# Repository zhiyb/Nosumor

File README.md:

# USB Mix

Design a small USB keyboard for playing [osu!](https://osu.ppy.sh/): [Blog posts](https://zhiyb.wordpress.com/category/cc/embedded/nosumor/)

In addition to mandatory keyboard functionalities, USB audio and Micro SD support are also added. So it's now called USB Mix.

The PCB layout was made compatible with [the original Nosumor v3 casing](http://noodlefighter.com/工作日志/log_nono/), which sells on [the official osu! store](https://osu.ppy.sh/store/product/20).

However, as a hobby project for learning USB framework and achieving high performance, the parts used in this design are probably unnecessarily expensive.

## Features

- USB 2.0 high-speed connection with 8kHz polling rate
- 5 switches (2x Cherry MX switches & 3x tactile switches)
- RGB lighting!
- Audio output through headphone jack using USB audio class 2
- Micro SD card reader
- Application for dynamic reconfiguration and firmware upgrade

### Planned features

- Audio input (MIC) through headphone jack
- MPU-9250 9-axis motion sensor
- ADC waveform capture
- DAC waveform generation

## PCB features

- 50×50 (mm) board area
- 2 mechanical keyboard switches (Cherry MX RGB compatible) and 3 tactile buttons
- Keycap and bottom-side RGB lighting
- STM32F722RE Cortex-M7 high performance MCU @216MHz
- USB 2.0 high-speed PHY USB3370
- 3.5mm audio jack with TLV320AIC3110 audio codec
- InvenSense MPU-9250 9-axis motion sensor
- On-board FT2232D connected to UART & JTAG for debugging
- Test points for 2xADC & 1xDAC
- Extension UART port with 3.3V power

Gerber files for PCB manufacturer Seeed Studio provided.

## Estimated costs

Configuration | Cost
---|---
Basic keyboard | £20
With audio and Micro SD slot | £30
Also with debugging USB port | £38

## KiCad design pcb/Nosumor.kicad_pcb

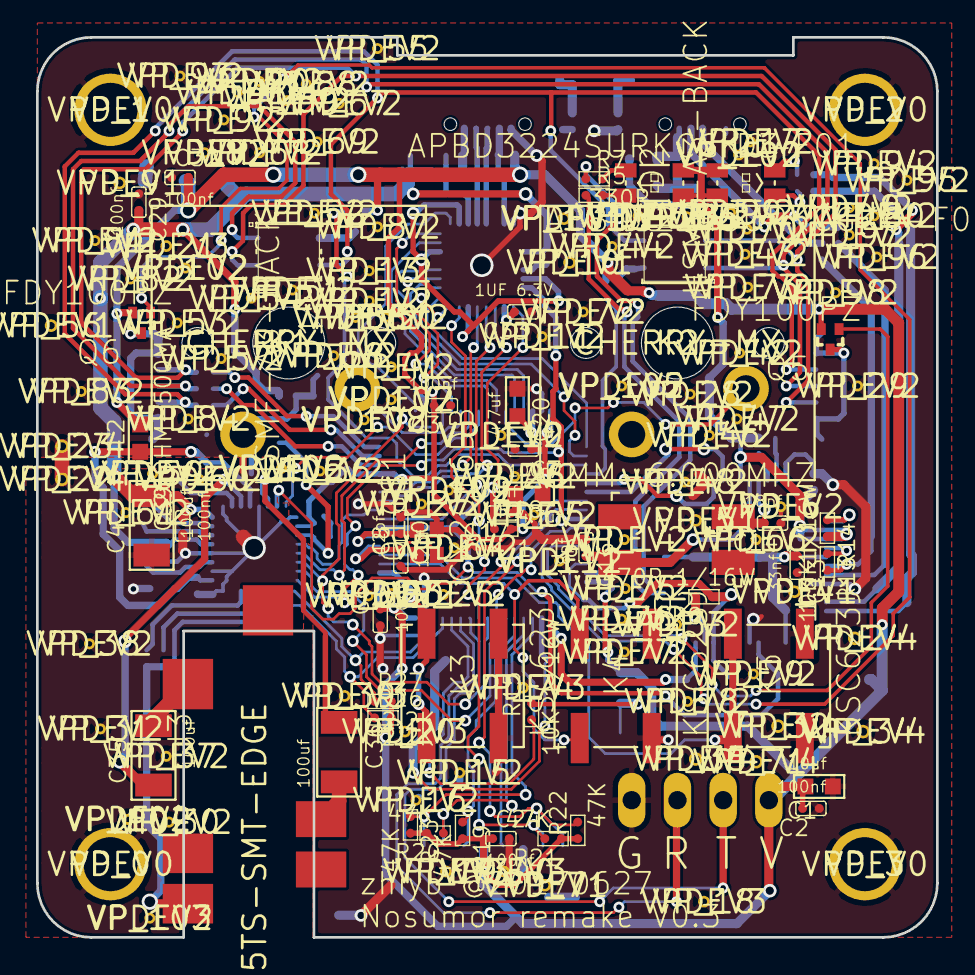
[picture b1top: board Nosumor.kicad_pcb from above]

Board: 2 copper layers, 50.0 x 50.0 mm, 223 parts (0 on the bottom side), 105 nets.

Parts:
3V3: TPB1,27; B1_27
BOOT316: 0R-JUMPB; B0R-JMP
C1, C23, C27, C37, C40: 10uf; C0603
C2, C3, C4, C5, C6, C9, C15, C17, C18, C19, C21, C22, C24, C25, C26, C28, C29, C31, C32, C38, C39, C41, C43, C44: 100nf; C0402
C7, C20: 4.7uf; C0603
C8, C10: 12pf; C0402
C11: 10nf; C0402
C12, C30, C33: 1UF 6.3V; C0402
C13: 33nf; C0402
C14, C16: 18pf; C0402
C34: 470nf; C0402
C35, C36, C42: 100uf; C1206
CLK316: TPB1,27; B1_27
D1, D2: HSMF-A3-BACK
D3, D5: APBD3224SURKCGKC-F01; 1210
D4, D6: MSL0104RGBU1; 2709
DIO316: TPB1,27; B1_27
GND316: TPB1,27; B1_27
IC1: STM32F722RET; LQFP64
IC2: REG1117; SOT223
IC3: TPS77018; SOT23-DBV
J1, J4: 629105136821
J2: 693071010811
J3: SJ-43515TS-SMT-EDGE; SJ-4351*-SMT-MIRRORED-EDGE
K1, K2: CHERRY-MX
K3, K4, K5: KSC623J; KSC-J
L1, L2, L3: 120OHM-500MA; L0603
Q1G$1: CX2016DB
Q2: ABMM-6.000MHZ; ABMM
Q3, Q4, Q5, Q6: FDY100PZ; SC-89
R4, R5, R6, R7: 330R; R0402
R8, R9: 470R 1/16W; R0402
R10, R11, R12: 150R; R0402
R13: 1.5K; R0402
R14, R15, R18, R28, R30: 10K 1/16W; R0402
R16, R17: 22R; R0402
R19, R20, R21, R22, R23: 47K; R0402
R26, R27, R31: 2.2K; R0402
R29: 20K; R0402
RST316: TPB1,27; B1_27
SLM316: TPB1,27; B1_27
SLP316: TPB1,27; B1_27
SRM316: TPB1,27; B1_27
SRP316: TPB1,27; B1_27
U1: LQFP48
U2: USB3370; QFN32
U3: TLV320AIC3110; VQFN32
UART316: 1X04
VP_0, VP_1, VP_2, VP_3: VPDEV0; VPAC0
VP_4, VP_5, VP_7, VP_9, VP_10, VP_56, VP_101: VPDEV1; VPAC1
VP_6, VP_8, VP_11, VP_12, VP_13, VP_14, VP_15, VP_16, VP_17, VP_25, VP_26, VP_27, VP_28, VP_29, VP_30, VP_31, VP_33, VP_36, VP_37, VP_38, VP_41, VP_42, VP_43, VP_44, VP_45, VP_46, VP_47, VP_48, VP_49, VP_50, VP_51, VP_52, VP_53, VP_54, VP_55, VP_57, VP_58, VP_59, VP_60, VP_61, VP_62, VP_63, VP_64, VP_65, VP_66, VP_67, VP_68, VP_69, VP_70, VP_72, VP_73, VP_75, VP_76, VP_77, VP_78, VP_79, VP_80, VP_81, VP_82, VP_83, VP_84, VP_85, VP_86, VP_87, VP_88, VP_89, VP_90, VP_91, VP_92, VP_93, VP_94, VP_95, VP_96, VP_97, VP_98, VP_99, VP_100, VP_102, VP_103, VP_104, VP_105, VP_106, VP_107, VP_108, VP_109, VP_110, VP_111: VPDEV2; VPAC2
VP_18, VP_19, VP_20, VP_21, VP_39, VP_40, VP_74: VPDEV3; VPAC3
VP_22, VP_23, VP_24, VP_32, VP_34, VP_35, VP_71: VPDEV4; VPAC4

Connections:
+1V8: C26.2, IC3.5, U3.3
+3V3: 3V3.TP, BOOT316.1, C1.2, C2.2, C3.2, C4.2, C5.2, C6.2, C7.2, C11.2, C12.2, C15.2, C24.1, C25.2, C32.2, IC1.1, IC1.13, IC1.19, IC1.32, IC1.48, IC1.64, IC2.2, J2.4, L2.2, Q3.3, Q4.3, Q5.3, Q6.3, R18.2, R19.2, R20.2, R21.1, R22.1, R23.2, R26.2, R27.2, R30.2, U3.2, UART316.1
+5V: C29.2, C38.2, C39.2, C40.2, C41.2, C42.2, IC2.3, IC3.1, L3.1, R29.2, U2.11, U3.21, U3.24
/AIC_BCLK: IC1.42, IC1.55, U3.7
/AIC_DIN: IC1.23, U3.5
/AIC_DOUT: IC1.9, U3.4
/AIC_GPIO: IC1.24, U3.32
/AIC_SCL: IC1.61, R26.1, U3.10
/AIC_SDA: IC1.62, R27.1, U3.9
/AIC_WCLK: IC1.20, IC1.56, U3.6
/BOOT0: IC1.60, R15.1
/DBG_5V: C19.2, C22.2, C23.2, D3.1, D3.3, D5.1, D5.3, L1.1, R9.2, R14.2, U1.3, U1.4, U1.42
/DBG_RXD: IC1.37, U1.39
/DBG_RX_LED: R7.1, U1.28
/DBG_SWD_LED1: R6.1, U1.12
/DBG_SWD_LED2: R4.1, U1.11
/DBG_TXD: IC1.38, U1.40
/DBG_TX_LED: R5.1, U1.27
/KEY_1: IC1.22, K1.SW1
/KEY_2: IC1.27, K2.SW1
/KEY_3: IC1.2, K3.1, K3.3
/KEY_4: IC1.3, K4.1, K4.3
/KEY_5: IC1.4, K5.1, K5.3
/LED_1: IC1.35, Q3.1
/LED_2: IC1.36, Q4.1
/LED_3: IC1.44, Q5.1
/LED_4: IC1.43, Q6.1
/MCLK: IC1.41, U2.15, U3.8
/MMC_CD: IC1.50, J2.10, J2.10-1
/MMC_CLK: IC1.53, J2.5
/MMC_CMD: IC1.54, J2.3, R19.1
/MMC_D0: IC1.39, J2.7, R21.2
/MMC_D1: IC1.40, J2.8, R22.2
/MMC_D2: IC1.51, J2.1, R23.1
/MMC_D3: IC1.52, J2.2, R20.1
/N$1: C35.2, J3.2
/N$4: J4.3, U2.5
/N$5: J4.2, U2.4
/N$6: J4.4, R30.1, U2.7
/N$7: SLP316.TP, U3.22
/N$8: J1.2, R16.2
/N$9: R13.2, R17.1, U1.7
/N$10: C13.1, U1.6, U1.14, U1.31
/N$11: C9.1, R9.1, U1.46
/N$12: D3.4, R6.2
/N$13: C18.2, J1.1, L1.2
/N$14: R13.1, U1.5
/N$15: R16.1, U1.8
/N$16: J1.3, R17.2
/N$17: R14.1, U1.2
/N$18: C14.2, Q2.1, U1.44
/N$19: C16.2, Q2.3, U1.43
/N$20: D5.4, R7.2
/N$21: D5.2, R5.2
/N$23: D3.2, R4.2
/N$24: C8.2, IC1.5, Q1G$1.1
/N$25: R8.2, U1.23
/N$26: C10.2, IC1.6, Q1G$1.3
/N$27: BOOT316.2, R15.2
/N$28: D6.1, D6.2, D6.6, D6.7, Q6.2
/N$29: C20.2, IC1.30
/N$30: SLM316.TP, U3.19
/N$31: C43.2, J4.1, L3.2
/N$32: R29.1, U2.13
/N$33: C30.2, U2.2, U2.14, U2.22, U2.30
/N$34: D1.2, Q3.2
/N$36: C33.2, U2.18
/N$37: R28.2, U2.3
/N$38: D4.1, D4.2, D4.6, D4.7, Q5.2
/N$39: D2.2, Q4.2
/N$40: D1.3, D2.3, D4.5, D6.5, R12.2
/N$41: D1.1, D2.1, D4.4, D6.4, R11.2
/N$42: D1.4, D2.4, D4.3, D6.3, R10.2
/N$44: SRP316.TP, U3.26
/N$45: SRM316.TP, U3.23
/N$46: C34.1, U3.14
/N$48: C36.1, U3.30
/N$49: R31.1, U3.12
/N$50: C35.1, U3.27
/N$51: C27.2, C28.2, C31.2, C37.2, L2.1, U3.17, U3.28
/RGB2_B: IC1.16, R10.1
/RGB2_G: IC1.15, R12.1
/RGB2_R: IC1.14, R11.1
/SRST_N: C17.2, IC1.7, R18.1, RST316.TP, U1.17, U2.17, U3.31
/SWCLK: CLK316.TP, IC1.49, U1.24
/SWDIO: DIO316.TP, IC1.46, R8.1, U1.22
/UART_RX: IC1.59, UART316.3
/UART_TX: IC1.58, UART316.2
/ULPI_CLK: IC1.21, U2.27
/ULPI_D0: IC1.17, U2.1
/ULPI_D1: IC1.25, U2.32
/ULPI_D2: IC1.26, U2.31
/ULPI_D3: IC1.28, U2.28
/ULPI_D4: IC1.29, U2.26
/ULPI_D5: IC1.33, U2.25
/ULPI_D6: IC1.34, U2.24
/ULPI_D7: IC1.57, U2.23
/ULPI_DIR: IC1.10, U2.19
/ULPI_NXT: IC1.11, U2.21
/ULPI_STP: IC1.8, U2.20
GND: BOOT316.3, C1.1, C2.1, C3.1, C4.1, C5.1, C6.1, C7.1, C8.1, C9.2, C10.1, C11.1, C12.1, C13.2, C14.1, C15.1, C16.1, C17.1, C18.1, C19.1, C20.1, C21.1, C22.1, C23.1, C24.2, C25.1, C26.1, C27.1, C28.1, C29.1, C30.1, C31.1, C32.1, C33.1, C37.1, C38.1, C39.1, C40.1, C41.1, C42.1, C43.1, C44.1, GND316.TP, IC1.12, IC1.18, IC1.31, IC1.47, IC1.63, IC2.1, IC3.2, IC3.3, J1.5, J2.6, J2.9, J2.9-1, J3.4, J4.5, K1.SW2, K2.SW2, K3.2, K3.4, K4.2, K4.4, K5.2, K5.4, R28.1, U1.9, U1.18, U1.25, U1.34, U1.45, U1.47, U2.8, U2.EXP, U3.1, U3.16, U3.18, U3.20, U3.25, U3.29, U3.EXP, UART316.4, VP_0.VP, VP_1.VP, VP_2.VP, VP_3.VP, VP_4.VP, VP_5.VP, VP_6.VP, VP_7.VP, VP_8.VP, VP_9.VP, VP_10.VP, VP_11.VP, VP_12.VP, VP_13.VP, VP_14.VP, VP_15.VP, VP_16.VP, VP_17.VP, VP_18.VP, VP_19.VP, VP_20.VP, VP_21.VP, VP_22.VP, VP_23.VP, VP_24.VP, VP_25.VP, VP_26.VP, VP_27.VP, VP_28.VP, VP_29.VP, VP_30.VP, VP_31.VP, VP_32.VP, VP_33.VP, VP_34.VP, VP_35.VP, VP_36.VP, VP_37.VP, VP_38.VP, VP_39.VP, VP_40.VP, VP_41.VP, VP_42.VP, VP_43.VP, VP_44.VP, VP_45.VP, VP_46.VP, VP_47.VP, VP_48.VP, VP_49.VP, VP_50.VP, VP_51.VP, VP_52.VP, VP_53.VP, VP_54.VP, VP_55.VP, VP_56.VP, VP_57.VP, VP_58.VP, VP_59.VP, VP_60.VP, VP_61.VP, VP_62.VP, VP_63.VP, VP_64.VP, VP_65.VP, VP_66.VP, VP_67.VP, VP_68.VP, VP_69.VP, VP_70.VP, VP_71.VP, VP_72.VP, VP_73.VP, VP_74.VP, VP_75.VP, VP_76.VP, VP_77.VP, VP_78.VP, VP_79.VP, VP_80.VP, VP_81.VP, VP_82.VP, VP_83.VP, VP_84.VP, VP_85.VP, VP_86.VP, VP_87.VP, VP_88.VP, VP_89.VP, VP_90.VP, VP_91.VP, VP_92.VP, VP_93.VP, VP_94.VP, VP_95.VP, VP_96.VP, VP_97.VP, VP_98.VP, VP_99.VP, VP_100.VP, VP_101.VP, VP_102.VP, VP_103.VP, VP_104.VP, VP_105.VP, VP_106.VP, VP_107.VP, VP_108.VP, VP_109.VP, VP_110.VP, VP_111.VP
unnamed: C36.2, J3.3
unnamed: C34.2, J3.1, R31.2, U3.11
unnamed: C21.2, J1.SHELL, J1.SHELL1, J1.SHELL2, J1.SHELL3
unnamed: C44.2, J4.SHELL, J4.SHELL1, J4.SHELL2, J4.SHELL3

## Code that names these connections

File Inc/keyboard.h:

#ifndef KEYBOARD_H
#define KEYBOARD_H

// Port A
#define LED_GPIO  GPIOA
#define LED_LEFT  GPIO_PIN_1
#define LED_RIGHT GPIO_PIN_2
#define LED_BLUE  GPIO_PIN_3
#define LED_GREEN GPIO_PIN_4
#define LED_RED   GPIO_PIN_5

// Port B
#define KEY_GPIO  GPIOB
#define KEY_LEFT  GPIO_PIN_9
#define KEY_RIGHT GPIO_PIN_10
#define KEY_1     GPIO_PIN_13
#define KEY_2     GPIO_PIN_14
#define KEY_3     GPIO_PIN_15

#endif // KEYBOARD_H

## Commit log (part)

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2017-06-25 USB HS initial
2017-06-28 USB setup initial
2017-06-29 Audio ADC loopback test
2017-06-29 Sine wave generation for audio testing
2017-07-05 USB Keyboard initial
2017-07-05 String descriptors, USB HID keyboard descriptors
2017-07-06 Keyboard interrupts initial
2017-07-06 Report all 5 keys
2017-07-06 Keyboard report initial
2017-07-06 Fix keyboard debouncing
2017-07-12 Nosumor PCB V0.3 USB audio initial
2017-07-19 SDMMC overclocks to 72MHz (more tests needed)
2017-07-19 Audio codec with DMA transmit initial
2017-07-20 Image of audio codec 192kHz sample frequency clock configuration
2017-07-24 USB Audio volume control initial
2017-07-24 USB implement more requests
2017-07-31 USB HID vendor device
2017-07-31 Host hidapi initial
2017-08-01 SD V2.00 SDSC support
2017-08-01 Host module separation, uses spdlog for logging
2017-08-01 IAP working
2017-08-02 Move flash functions to ITCM RAM
2017-08-10 Fix host HID application on Linux
2017-09-01 USB Audio Class 2 initial
2017-09-07 UAC2 + codec play but noisy
2017-09-08 UAC2 structural update, clock selector initial
2017-09-09 UAC2 reduce noise
2017-09-09 Audio volume display in debug build
2017-09-09 Optimise audio reconfiguration
2017-09-10 USB Audio Class 2 with feedback endpoint
2017-09-11 USB audio structural rewrite
2017-09-11 More detailed panic debugging information
2017-09-12 USB audio structural rewrite complete
2017-09-12 Feature unit for headphones
2017-09-12 Move some small functions into feature units
2017-09-12 Feature unit for analog attenuation
2017-09-12 Mute only so that DAC volume will be used as the main volume
2017-09-12 Reduce audio buffering space, reduce audio latency
2017-09-12 Fix audio endpoint disabling
2017-09-13 Improve audio reliability, disable isochronous incomplete interrupt if not needed
2017-09-13 Use dedicated interrupt for endpoint 1 (audio)
2017-09-13 Move keyboard mismatch debugging output outside critical region
2017-09-22 Improve audio data rate feedback, reduce audio buffer size
2017-09-23 Keycode update using HID vendor-defined interface
2017-09-26 Update software version to 0x0004
2017-10-12 Initial README.md
2017-11-10 USB MSC initial
2017-11-10 USB fix for endpoint 0 halting control under debug
2017-11-10 Add USB mass storage interface in debug build
2017-11-19 KiCad PCB conversion initial
2017-12-17 Host/Qt: GUI application initial
2017-12-18 Host: Plugins
2017-12-18 host/plugins/ping: Correct header file definitions
2017-12-18 host/plugins/keycode: Keycode update
2017-12-18 host/plguins/keycode: Remove unsued parameter warning
2017-12-18 host: Support for MSVC 2017 compiler
2017-12-23 host/plugins/keycode: Keycode conversion from keyboard key press
2017-12-24 host/plugins/keycode: All keyboard usage IDs
2018-01-01 Add product name macro define
2018-01-01 debug: Flush stdout on debug breakpoints
2018-01-01 device/usb/msc/scsi: Vital product data: Unit serial number page
2018-01-01 device/usb/msc/scsi: READ CAPACITY (10)
2018-01-01 device/usb/msc/scsi: READ (10) initial
2018-01-01 device/usb/msc/scsi: Ignore SYNCHRONIZE CACHE (10)
2018-01-01 device/usb/msc/scsi: Ignore START STOP UNIT
2018-01-01 device/usb/msc/scsi: Simulate 64kiB RAM disk
2018-01-01 device/usb/msc/scsi: Improve command implementation check
2018-01-01 device/usb/msc/scsi: WRITE (10) initial
2018-01-01 device/usb/msc/scsi: Fix block write
2018-01-01 device/peripheral/mmc: Calculate card capacity
2018-01-01 device/peripheral/mmc: SCSI interface functions initial
2018-01-01 device/usb/msc: Check for MSC accessibility
2018-01-01 device: Add SD/MMC and USB MSC to release build
2018-01-02 device/peripheral/mmc: RX DMA initial
2018-01-02 device: Update CMSIS, use UID and FLASHSIZE from CMSIS
2018-01-02 device: Move heap to DTCM region for data cache
2018-01-02 device: Enable I-Cache and D-Cache
2018-01-02 device/vendor: Move report to DTCM for cache coherency
2018-01-02 device/debug: Improve panic message
2018-01-03 device/macros: Static assertion
2018-01-03 device/peripheral/mmc: TX DMA initial
2018-01-03 device/usb/msc: Double buffering
2018-01-03 device: Only show debug statistics when updated
2018-01-03 device/peripheral/mmc, device/usb/msc/scsi: Break apart write process, improve performance
2018-01-04 device/peripheral/mmc, device/usb/msc/scsi: Use DMA for both RX and TX
2018-01-04 device/clocks: Increase MCO1 GPIO speed
2018-01-04 device/peripheral/mmc, device/usb/msc: Start data transfer before read completion, improved performance
2018-01-04 device/usb: Add status return to IN endpoint transfer
2018-01-04 device/usb: Move endpoint initialisations after set configuration
2018-01-04 host/qt: Refresh device list on gaining window focus
2018-01-05 device/usb: Do not ignore IN endpoint data with NAKSTS set
2018-01-06 device/peripheral/audio: Sin wave for audio testing
2018-01-07 device: Show USB RAM usage for debugging
2018-01-07 device/usb/audio2: Support for multi-packet transfer
2018-01-07 device/usb: Fix USB RAM allocation start address issue
2018-01-07 device: Remove audio test key, since UAC2 now works with MSC
2018-01-07 device/clocks: Add timer clock frequency calculations
2018-01-07 device/peripheral/rgb: RGB and scan timer hierarchy initial
2018-01-08 device/vendor: RGB set descriptor initial
2018-01-08 device/clocks: Add DCKCFGR1 to timer clock frequency calculation
2018-01-08 device/vendor: Update report formats for RGB LED support
2018-01-08 device/vendor: Fix LED config packet size check and RGB ordering
2018-01-08 host/plugins/led: LED configuration plugin
2018-01-08 device/peripheral/led: Fix intensity precision issue
2018-01-08 device/peripheral/audio: Faster recovery from lost sync
2018-01-08 device/usb/msc/scsi: Use block as address and length unit
2018-01-08 device: More escape sequences
2018-01-08 device/peripheral/mmc: Hot plug support initial
2018-01-08 device/peripheral: Miscellaneous
2018-01-09 device/peripheral/mmc: Status report for interrupted read/write operations
2018-01-09 device/usb/msc: Support for hot plug during write operations
2018-01-09 device/peripheral/mmc: Improve hot plug stability
2018-01-09 device: Split main and bootloader projects
2018-01-09 device/peripheral/mmc: Use weak alias for SCSI functions
2018-01-10 device/usb: Fixed a bug when host requested a 64-byte descriptor
2018-01-10 device/flash_scsi: SCSI interface flash operations initial
2018-01-10 device/FatFs: Rename SD to MMC
2018-01-10 device/usb/msc/scsi: Support for different product names
2018-01-10 device: Use flash partitions as SCSI & FatFs devices initial
2018-01-10 device/usb/msc/scsi: Add removable as device type
2018-01-10 device: Directory structure update
2018-01-10 device/usb/msc: Fix potential cacheing issue with data prefetch
2018-01-10 device/usb/msc: Instead of flushing cache, use DTCM section
2018-01-10 device: Attach shadow configuration partition to main
2018-01-11 PCB: New revision (v0.4) inital
2018-01-12 PCB: Revision 1.0, silkscreen checked
2018-01-13 PCB: Move a few things around (power supply rails)
2018-01-13 device: Miscellaneous fixes for release build
2018-01-13 device/usb/msc: Improve performance by storing the currently active LUN
2018-01-21 device/logic/vendor: I2C control initial
2018-01-21 device/peripheral/audio: Proper audio reset
2018-01-21 host/plugins/i2c: Handle return presses
2018-01-23 pcb: Corrections to BOM
2018-01-23 device/peripheral/keyboard: Support for PCB revision 1.0
2018-01-23 device/peripheral/mmc: Support for PCB revision 1.0
2018-01-23 device/peripheral/led: Support for PCB revision 1.0
2018-01-26 device/peripheral/keyboard: Add #define keyboard masks
2018-01-27 device/logic/led_trigger: Trigger implementation initial
2018-01-28 device/logic/led_trigger: Multiple evaluation channel support
2018-01-28 device/logic/led_trigger: Use floating point numbers for colour normalisation
2018-01-31 device/ld: Update linker scripts to bootloader + app layout
2018-02-01 device: Miscellaneous optimisation for bootloader
2018-02-01 device/system/flash: Miscellaneous fixes and stability improvements
2018-02-01 device/peripheral/led: Structural update, support for PCB revision 0.2
2018-02-01 device: Miscellaneous performance improvements
2018-02-02 device: Try new qbs project structure
2018-02-03 device/peripheral/audio, device/usb/audio2/usb_audio2: Skip UAC2 initialisation if audio codec was not found
2018-02-04 device/peripheral/mpu: MPU9250 initial
2018-02-05 device/peripheral/i2c: Generalise I2C & DMA base addresses
2018-02-05 device/peripheral/i2c: Interrupt mode read & write operations
2018-02-05 device/peripheral/i2c: Miscellaneous improvements
2018-02-06 device/peripheral/i2c: Add register address as a parameter to i2c_write
2018-02-07 device/peripheral/audio: Multi-byte I2C transfer for configuration updates
2018-02-08 device/peripheral/i2c: Support for TX DMA & non-blocking write
2018-02-08 device/peripheral/audio: Do not register UAC if codec not found
2018-02-09 device/peripheral/mpu: Connect MPU to USB HID joystick
2018-02-09 device/usb/hid/joystick: Add 5 buttons
2018-02-10 device/peripheral/mpu: Miscellaneous
2018-02-11 device/peripheral/mpu: Sample update counter
2018-02-12 device/peripheral/mmc: Use double buffering for read
2018-02-12 device/peripheral/i2c: Miscellaneous
2018-02-12 device/peripheral/mmc: Multiple read buffers
2018-02-13 device/logic/scsi: Output potential data before read complete
2018-02-13 device/peripheral/mmc: Combine continuous buffer space
2018-02-13 device/peripheral/mmc: Multi-block transfer
2018-02-14 device/system_stm32f7xx: Improve fault debugging output
2018-02-14 device/system_stm32f7xx: Separate hard fault handler
2018-02-15 device: Fix occasional crash from memory allocation
2018-02-15 device: Update CMSIS
2018-02-17 device/api: Change logic/vendor to api, initial support for configuration channels
2018-02-17 Move device/logic/api_proc to device/api/api_proc
2018-02-17 host: Miscellaneous
2018-02-17 device/api/api_led: RGB LED configuration API
2018-02-18 host: Plugin version check
2018-02-18 host/plugins/i2c: Support for newer implementation
2018-02-19 device/peripheral/keyboard: Get keycode and key names
2018-02-19 host/plugins/keycode: Key code read back
2018-02-19 host/plugins/led: Use payload size to determine operation
2018-02-19 host/console, host/plugins/info: Payload size of 0 as channel count report
2018-02-20 device/api/api_config: System configurations initial, keyboard & joystick update enable
2018-02-20 device/api/api_config: Connect/disconnect MicroSD & Flash
2018-02-22 device/usb/hid/mouse: USB HID mouse initial
2018-02-22 device/peripheral/mpu: Gyroscope minimal integration implementation
2018-02-23 device/motion_driver/core/driver/eMPL: Port driver to device
2018-02-23 device/peripheral/mpu: Initial test for motion_driver
2018-02-23 device/peripheral/mpu: Non-blocking FIFO packet read
2018-02-23 host/plugins/motion: Render device orientation from quaternion report
2018-02-23 device/peripheral/mpu: Report accelerometer & gyroscope values
2018-02-23 host/plugins/plugin: OUT report retry
2018-02-23 host/plugins/motion: Option to disable updating 3D model
2018-02-24 device/eMPL: Parse compass data from existing register content
2018-02-24 device/api/api_motion: Report compass data
2018-02-25 device/peripheral/mpu: Add axes orientation correction
2018-02-25 host/plugins/motion: Show top view
2018-02-25 host/plugins/motion: Use vertex array objects
2019-03-05 PCB version 1.1 connected
2019-03-12 PCB with silkscreen
2019-04-09 Restart project, because why not
2019-04-11 Use link time list to store event handlers
2019-04-15 Update PCB BOM, fix miscellaneous schematic markings
2019-04-15 USB endpoint reservation initial
2019-04-24 PCB revision 1.2, fix RGB LED footprint
2019-11-08 Initial common files
2019-11-09 USB enumeration initial
2019-11-10 Better implementation of link time list
2019-12-23 PCB revision 1.3 with USB Type-C, more datasheets
2020-01-15 USB OUT initial
2020-04-27 USB configuration descriptor done
2020-04-27 device: USB HID keyboard initial
2020-04-27 USB HID vendor initial
2020-04-28 device: Use -O3 for memory test
2020-04-28 device: Memory test repeat 4 times
